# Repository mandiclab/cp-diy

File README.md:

# CP-DIY
**Control Pad**

## 🌐 Community & Support

**You can support the project by donating on Ko-fi.**
- [Ko-fi](https://ko-fi.com/mandiclab)

**Stay connected, get updates, ask questions.**
- [Discord Server](https://discord.gg/aApBQxZUcu)
- [Web Site](https://www.mandiclab.com/)
- [YouTube](https://www.youtube.com/@mandiclab)
- [Instagram](https://www.instagram.com/mandiclab/)  
- [TikTok](https://www.tiktok.com/@mandiclab)

## 📜 Licenses

- **Software** (.ino):  
  Licensed under the [GPL-3.0](LICENSE-SOFTWARE.txt)

- **Hardware** (.FCStd, .stl, .pretty, .kicad_mod, .kicad_pcb, .kicad_pro, .kicad_sch, .kicad_sym):  
  Licensed under the [CERN-OHL-S-2.0](LICENSE-HARDWARE.txt)

Made With Love - MandićLab

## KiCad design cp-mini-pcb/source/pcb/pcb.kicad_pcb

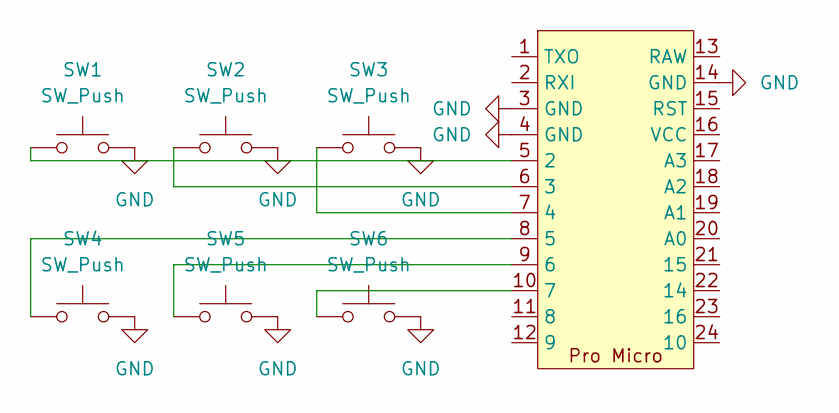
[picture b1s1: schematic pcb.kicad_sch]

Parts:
SW1, SW2, SW3, SW4, SW5, SW6: SW_Push; SW_SPST_Omron_B3F-40xx
U1: pro-micro

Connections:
GND: SW1.2, SW2.2, SW3.2, SW4.2, SW5.2, SW6.2, U1.3 (GND), U1.4 (GND), U1.14 (GND)
unnamed: SW1.1, U1.5 (2)
unnamed: SW2.1, U1.6 (3)
unnamed: SW3.1, U1.7 (4)
unnamed: SW4.1, U1.8 (5)
unnamed: SW5.1, U1.9 (6)
unnamed: SW6.1, U1.10 (7)

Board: 2 copper layers, 7 parts (0 on the bottom side), 7 nets, no tracks yet.

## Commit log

2025-10-03 add license
2025-10-03 add readme
2025-10-14 add .gitignore and front panel model
2025-10-18 fix .gitignore
2025-10-18 add case
2025-10-18 (case) add hole for wires
2025-10-18 add case.stl
2025-10-18 change file structure
2025-10-18 fix file structure
2025-10-18 add (front-panel) add diffuser support
2025-10-18 add diffuser
2025-10-18 add front-panel.stl
2025-10-18 add diffuser.stl
2025-10-18 add arduino cover
2025-10-18 add arduino-cover.stl
2025-10-19 add cable cover
2025-10-19 add cable-cover.stl
2025-10-19 add button cap
2025-10-19 add button-cap.stl
2025-10-19 (case) decrease height of button socket
2025-10-23 (front panel) change diffuser socket
2025-10-23 (diffuser) change dimensions
2025-10-23 (case) add side hole for usb cable
2025-10-23 (diffuser) change design
2025-10-23 (button cap) fix height of button socket
2025-10-23 (arduino cover) change design
2025-10-23 (cable cover) change design
2025-10-23 add 3Dprint-settings.txt
2025-10-24 (arduino cover) increase width
2025-10-24 (button cap) decrease height and width of backplate
2025-10-24 (case) add snap-fit system
2025-10-24 (front panel) add snap-fit system
2025-10-24 (front panel) decrease radius of holes for snap-fit system
2025-10-28 add shared files from cp-mini to cp-regular
2025-10-28 add front panel
2025-10-28 add stand
2025-10-28 add stand.stl
2025-10-30 update .gitignore for KiCad
2025-10-30 add pcb
2025-11-03 (stand) add socket and cable hole
2025-11-03 upate stand,stl
2025-11-04 (stand) chamfer socket edges
